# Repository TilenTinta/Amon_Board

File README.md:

# Amon Board — Flight Controller & Firmware

**Project Status:** In Progress

# Description:
Flight controller hardware and firmware used in the Amon Lander project. Two hardware lines are maintained:
- **Board v1 (ESP32 WROOM-32)** — never released (critical error).
- **Board v2 (STM32F405)** — the current, working design.
- **Board v3 (STM32H743VIT6)** — in development.
- **Board v4 (STM32xxx (Zephyr) + Raspberry Pi CM4)** — the next-gen design with a new MCU running Zephyr RTOS and a companion **Raspberry Pi Compute Module 4 (CM4)**.

> Part of the Amon Lander project:
>
> - **Amon Lander** — overall vehicle, frame, test/control SW, and data  
>   https://github.com/TilenTinta/Amon_Lander  
> - **Amon Link** — PC - drone communications (PCB + firmware)  
>   https://github.com/TilenTinta/Amon_Link  
> - **Amon Ground Control** — desktop GCS for telemetry & control  
>   https://github.com/TilenTinta/Amon_GroundControl_Software

---

## Table of Contents

- [Overview](#overview)
- [Hardware Versions](#hardware-versions)
  - [Board v2 — STM32F405](#board-v1--stm32f405)
  - [Board v3 — STM32H743](#board-v1--stm32h743)
  - [Board v4 — Zephyr + CM4](#board-v2--zephyr--cm4)
- [Version Matrix](#version-matrix)
- [Repository Structure](#repository-structure)
- [Getting Started](#getting-started)
  - [Build & Flash: Board v2 & v3](#build--flash-board-v1)
  - [Build & Flash: Board v4 (Zephyr)](#build--flash-board-v2-zephyr)
  - [First Boot: CM4 Companion](#first-boot-cm4-companion)
- [Calibration & Testing](#calibration--testing)
- [Roadmap](#roadmap)
- [Status & Disclaimer](#status--disclaimer)
- [License](#license)
- [Acknowledgments](#acknowledgments)

---

## Overview

This board is a custom flight controller for **Amon Lander**. The **v2** generation uses an **STM32F405RGT6 (LQFP-64)** and a hand-written firmware stack (drivers from scratch, for learning and control). Because of the flight algorithm planned to be used in this project, the decision was made to modify the current **v2** PCB with a new MCU. This is the **STM32H743VIT6 (LQFP-100)** and to fix some issues and add features that were missing or incorrect in the previous version. A **v3** generation is being designed around a **Zephyr-supported MCU** for real-time control, that will be paired with a **Raspberry Pi CM4** for high-level tasks (GCS link, logging, navigation stack, future CV/ML, etc.) in **v4**.

Everything was built from the ground up — **electronics, firmware, and software**. Most tools used are **free** and widely available to makers. Expect a learning-first approach over simplicity: some solutions could be easier, but the point is to **learn and explore**.

---

## Hardware Versions

### Board v1 — ESP32 WROOM-32

**Highlights**

- **MCU:** ESP32 WROOM-32 module
- **Power & Protection**
  - Dual vertical **XT60** inputs (PCB PWR and EDF voltage)
  - **Reverse-polarity diode**
  - Max input tested: **12 V**
  - Two **LDO regulators**: 3.3V (MCU/sensors) & 5V/5A (servos)
- **Sensors**
  - **MPU6050** (IMU)
  - **BME280** (temp/pressure/humidity)
  - TOF connector for **VL53L1X**
- **Navigation & Comms**
  - **GPS** connector (GY-NEO6MV2)
  - **single NRF24L01+ PA/LNA** (RX–TX) module
  - **ESP32 WiFi** can be used for communication
- **I/O**
  - **PWM:** 4× servos + 1× EDF
  - Expansion: **SPI** & **I²C** headers
  - **USB** with surge protection (over CH340C)
  - **4-pin JTAG** header
  - **RGB status LED**
  - **Buzzer**
- **Storage:** **microSD** slot
- **PCB:** 4-layer

**Firmware (v1)**
- **Status:** Never really worked (ESP32 was eliminated from the project)

### Board v2 — STM32F405

**Highlights**

- **MCU:** STM32F405RGT6 (LQFP-64) - Cortex M4, 168MHz, 196kB RAM, 1MB Flash
- **Power & Protection**
  - Dual vertical **XT60** inputs (PCB PWR and EDF voltage)
  - **Reverse-polarity diode**
  - Max input tested: **12 V**
  - Two **buck regulators**: 3.3 V (MCU/sensors) & 5 V (servos), ~5 A each
- **Switching/Startup:** Power-on by battery insertion or external switch on a terminal
- **Grounding:** Grounded mounting holes
- **Sensors**
  - **MPU6050** (IMU)
  - **BME280** (temp/pressure/humidity)
  - **HMC5883L** (compass) *added later
  - TOF connector for **VL53L1X**
- **Navigation & Comms**
  - **GPS** connector (GY-NEO6MV2; also reused for calibration)
  - **2× NRF24L01+ PA/LNA** (RX–TX)
- **I/O**
  - **PWM:** 4× servos + 1× EDF (configurable)
  - Expansion: **SPI** & **I²C** headers
  - **USB OTG** with surge protection
  - **10-pin JTAG** header
  - **RGB status LED**
- **Storage:** External flash (telemetry) + **microSD** slot
- **PCB:** 4-layer, working but slated for a future revision/refresh

**Firmware (v2)**

- **Approach:** Minimal dependencies; **drivers from scratch** (for learning)  
- **Status:** Runs and evolves; some drivers may still have rough edges  
- **Focus:** Bring-up, sensor fusion, basic control loops, telemetry logging and transmition...

> 

### Board v3 — STM32H743

**Highlights**

- **MCU:** STM32H743VIT66 (LQFP-100) - Cortex M7, 480MHz, 1MB RAM, 2MB Flash
- **Power & Protection**
  - Dual horizontal **XT60** inputs (PCB PWR and EDF voltage)
  - **Reverse-polarity diode**
  - Max input tested: **12 V**
  - Three **buck regulators**: 3.3 V (MCU/sensors) & 5 V (ESC and placeholder) & 7.2 V (servos), ~5 A each + more stable voltage
- **Switching/Startup:** Power-on sequence 3.3V -> 5V -> 7.2V (monitoring of regulators output voltages and enable/disable function)
- **Grounding:** Grounded mounting holes
- **Sensors**
  - **MPU6050** (IMU)
  - **BME280** (temp/pressure/humidity)
  - **HMC5883L** (compass)
  - Connector for TOF - **VL53L1X**
  - Connector for optical flow - **PMW3901**
- **Navigation & Comms**
  - Connector for GPS module -**GY-NEO6MV2**
  - **2× NRF24L01+ PA/LNA** (RX–TX) now on PCB - eliminated use of modules
  - **USB** over serial chip (CH340G) - eliminated use of USB OTG
- **I/O**
  - **PWM:** 4× servos + 1× EDF
  - Expansion: **SPI** & **I²C** headers
  - **10-pin JTAG** header (Olimex HAB-VCR-010-LF)
  - **RGB status LED**
  - **Single RED status LED**
  - Three connector low **LED modules** and additional AUX connector for future use
- **Storage:** External flash (telemetry) + **microSD** slot
- **PCB:** 4-layer

**Firmware (v3)**

- **Base:** Firmware is fully based on **Firmware v2**
- **Approach:** Minimal dependencies; **drivers from scratch** (for learning)  
- **Status:** Runs and evolves; some drivers may still have rough edges  
- **Focus:** sensor fusion, advance control algorithms, telemetry logging and transmition...

> 

---

### Board v4 — Zephyr + CM4

**Architecture (planned / in development)**

- **Real-time MCU (Zephyr)**  
  - New MCU (TBD; Zephyr-supported) handles **Real-time**:
    - Sensor acquisition & fusion
    - Control loops (attitude/rate, TVC/actuators, EDF control)
    - Safety interlocks & failsafes
    - Deterministic logging (to QSPI flash / SD)
  - **Zephyr RTOS** app with:
    - Devicetree-based pin/peripheral config
    - Workqueues/threads for IMU, baro, magnetometer, TOF, PWM
    - Shell/CLI over UART/USB for diagnostics
    - Config storage (NVS) and firmware update hooks

- **Companion Computer — Raspberry Pi CM4**  
  - Runs services for:
    - Ground link, mission control, high-rate logging
    - Navigation stack expansion (mapping, state estimation helpers)
    - Future CV/ML applications (optional)
  - **Link to MCU:** UART (primary) + SPI/CAN (optional)  
  - **Services:** Telemetry bridge (to Amon Link), data recorder, configuration UI server
  - **OS:** Raspberry Pi OS Lite (or other lightweight Linux)

**Electrical**
- Robust power tree with multiple separated rails for servos/EDF vs logic
- MCU - CM4 isolation where needed (level shifting/ESD)
- On-board mass storage for logs (eMMC on CM4 + SD/QSPI on MCU)
- External debug: SWD/JTAG for MCU; USB-C or Ethernet for CM4

**Firmware (v4)**

- **Zephyr** application (modules: sensors, control, comms, storage)
- **IPC format:** CBOR/Protobuf frame over UART (CRC-guarded)
- **Bootloaders & Updates:** MCU bootloader (serial/DFU), CM4 apt-based or containerized deployment
- **Testing:** HIL hooks; replay logs for control tuning

---

## Version Matrix

## Version Matrix

| Capability                  | Board v1 — ESP32 | Board v2 — STM32F405 | Board v3 — STM32H743 | Board v4 — Zephyr + CM4 |
|----------------------------|------------------|----------------------|----------------------|--------------------------|
| MCU                         | ESP32 WROOM-32   | STM32F405RGT6        | STM32H743VIT6        | **TBD (Zephyr-supported)** |
| RTOS                        | None             | None (bare-metal)    | None (bare-metal)    | **Zephyr RTOS**          |
| Companion Computer          | —                | —                    | —                    | **Raspberry Pi CM4**     |
| Sensors                     | MPU6050, BME280, VL53L1X | MPU6050, BME280, HMC5883L, VL53L1X | MPU6050, BME280, HMC5883L, VL53L1X | Same class; final selection TBD |
| Radio                       | 1× NRF24L01+ PA/LNA | 2× NRF24L01+ PA/LNA | 2× NRF24L01+ PA/LNA | TBD (NRF / other via MCU or CM4) |
| Navigation                  | GPS (GY-NEO6MV2) | GPS (GY-NEO6MV2)     | GPS (GY-NEO6MV2)     | GPS via MCU or CM4 module |
| Storage                     | microSD          | Flash + microSD      | Flash + microSD      | CM4 eMMC + MCU flash/SD  |
| USB                         | USB (CH340C)     | USB OTG              | USB OTG + CH340G     | USB (MCU + CM4)          |
| Programming / Debug         | 4-pin JTAG       | 10-pin JTAG          | 10-pin JTAG          | SWD/JTAG (MCU) + SSH/USB/Ethernet (CM4) |
| PWM Outputs                 | 4× servos + 1× EDF | 4× servos + 1× EDF | 4× servos + 1× EDF | Same (handled by MCU)    |
| Expansion                   | SPI, I²C         | SPI, I²C             | SPI, I²C             | SPI, I²C, UART, CAN (planned) |
| Power                       | XT60, LDO (3.3V + 5V/5A) | XT60, buck (3.3V + 5V/5A + 7.2V) | XT60, improved buck (3.3V + 5V/5A) | Segregated rails, higher headroom (TBD) |
| PCB                         | 4-layer          | 4-layer              | 4-layer              | TBD                      |
| Firmware Status             | Not working    | Working, evolving | In development | In development        |
| Firmware Approach           | —                | Bare-metal, custom drivers | Based on v2, improved | Zephyr modules + Linux services |
| Firmware Updates            | USB              | JTAG/SWD/DFU         | JTAG/SWD/DFU         | MCU bootloader + CM4 (apt/container) |

---

## Getting Started

### Build & Flash: Board v1

1. **Clone**
   ```bash
   git clone https://github.com/<your-org-or-user>/Amon_Board.git
   cd Amon_Board/firmware/Amon_board_firmware-MCU
   ```
2. **Toolchain**
   - Install `arm-none-eabi-gcc` and your preferred STM32 flashing tool.
3. **Configure - can be automatic**
   - Target: **STM32F405RG**; enable FPU; set clock tree; verify linker script.
4. **Build**
   ```bash
   make
   ```
   or use your IDE’s Build action.
5. **Flash**
   - Via **JTAG/SWD** (10-pin header) using your probe (ST-Link, J-Link, etc.).
6. **Verify**
   - Rails at 5 V/3.3 V, sensor presence on I²C/SPI, status RGB LED patterns.

---

### Build & Flash: Board v2 (Zephyr)
Instructions bellow are only "place holder". Detailed instructions will be provided once the development will be started. For flashing and debugging will be used Segger Ozone software.

1. **Prerequisites**
   - Install **Zephyr SDK**, Python, CMake, Ninja.
   - Install **west**: `pip install west`
2. **Get Sources**
   ```bash
   cd Amon_Board/firmware/v2-zephyr
   west init -l .
   west update
   ```
3. **Board Definition**
   - Use the custom board under `boards/amon_v2/` (edit SoC, pins, clocks, and flash layout as needed).
4. **Build**
   ```bash
   west build -b amon_v2 app
   ```
5. **Flash**
   ```bash
   west flash
   ```
6. **Console**
   ```bash
   west espressif monitor   # or 'west zephyr monitor' / minicom, depending on target
   ```
   *(Choose the appropriate monitor command for your MCU/OS.)*

---

### First Boot: CM4 Companion

1. **Flash OS**
   - Install **Raspberry Pi OS Lite** to CM4’s eMMC or carrier-board storage.
2. **Enable Interfaces**
   - `sudo raspi-config` → enable UART, I2C, SPI as needed.
3. **Install Services**
   ```bash
   sudo apt update
   sudo apt install python3-pip git
   git clone https://github.com/<your-org-or-user>/amon-cm4-services.git
   cd amon-cm4-services && ./install.sh
   ```
   - Starts a telemetry bridge (serial↔TCP/gRPC), data logger, and config UI.
4. **Connect to MCU**
   - Wire UART (and optionally SPI/CAN) between CM4 and MCU.
   - Confirm link with a ping/handshake command.
5. **Network Access**
   - SSH into CM4; forward telemetry to **Amon Ground Control** over Wi-Fi/Ethernet.

---

## Calibration & Testing

- **GPS/Calibration Port:** The v2 GPS connector doubles as a calibration interface during bring-up. PCB v3 do this over USB.  
- **Telemetry:** Log to external flash/microSD (v2 & v3) or CM4 eMMC + MCU storage (v4).  
- **LED Status:** On-board RGB LED signals power, init, errors, and link status.  
- **HIL/Replay (v2):** Reproduce flights by streaming recorded sensor frames back into the MCU (for controller tuning).

---

## Roadmap

- **v1**
   - Failed design
- **v2**
  - Incremental driver fixes and documentation cleanup
  - Manufacturing files refresh (Gerbers/BOM/PNP)
- **v3**
   - Modified v2 design with new MCU, connectors, sensors
   - Modified v2 firmware for new MCU (much higher clock: 168 MHz -> 480MHz)
   - Development of flight algorithm and controller + first flights 
- **v4**
  - Finalize MCU choice and Zephyr board port
  - Define IPC schema (CBOR/Proto) & reliability (CRC/seq/ACK)
  - CM4 services (logger, bridge, config UI)
  - Development of new flight algorithm and controllers + flights 

---

## Status & Disclaimer

- **Works, but in progress:** v2 firmware runs; development is active and some drivers may still have rough edges.  
- **New hardware incoming:** v2/v3/v4 will introduce a Zephyr-based MCU and CM4 companion; designs are evolving.

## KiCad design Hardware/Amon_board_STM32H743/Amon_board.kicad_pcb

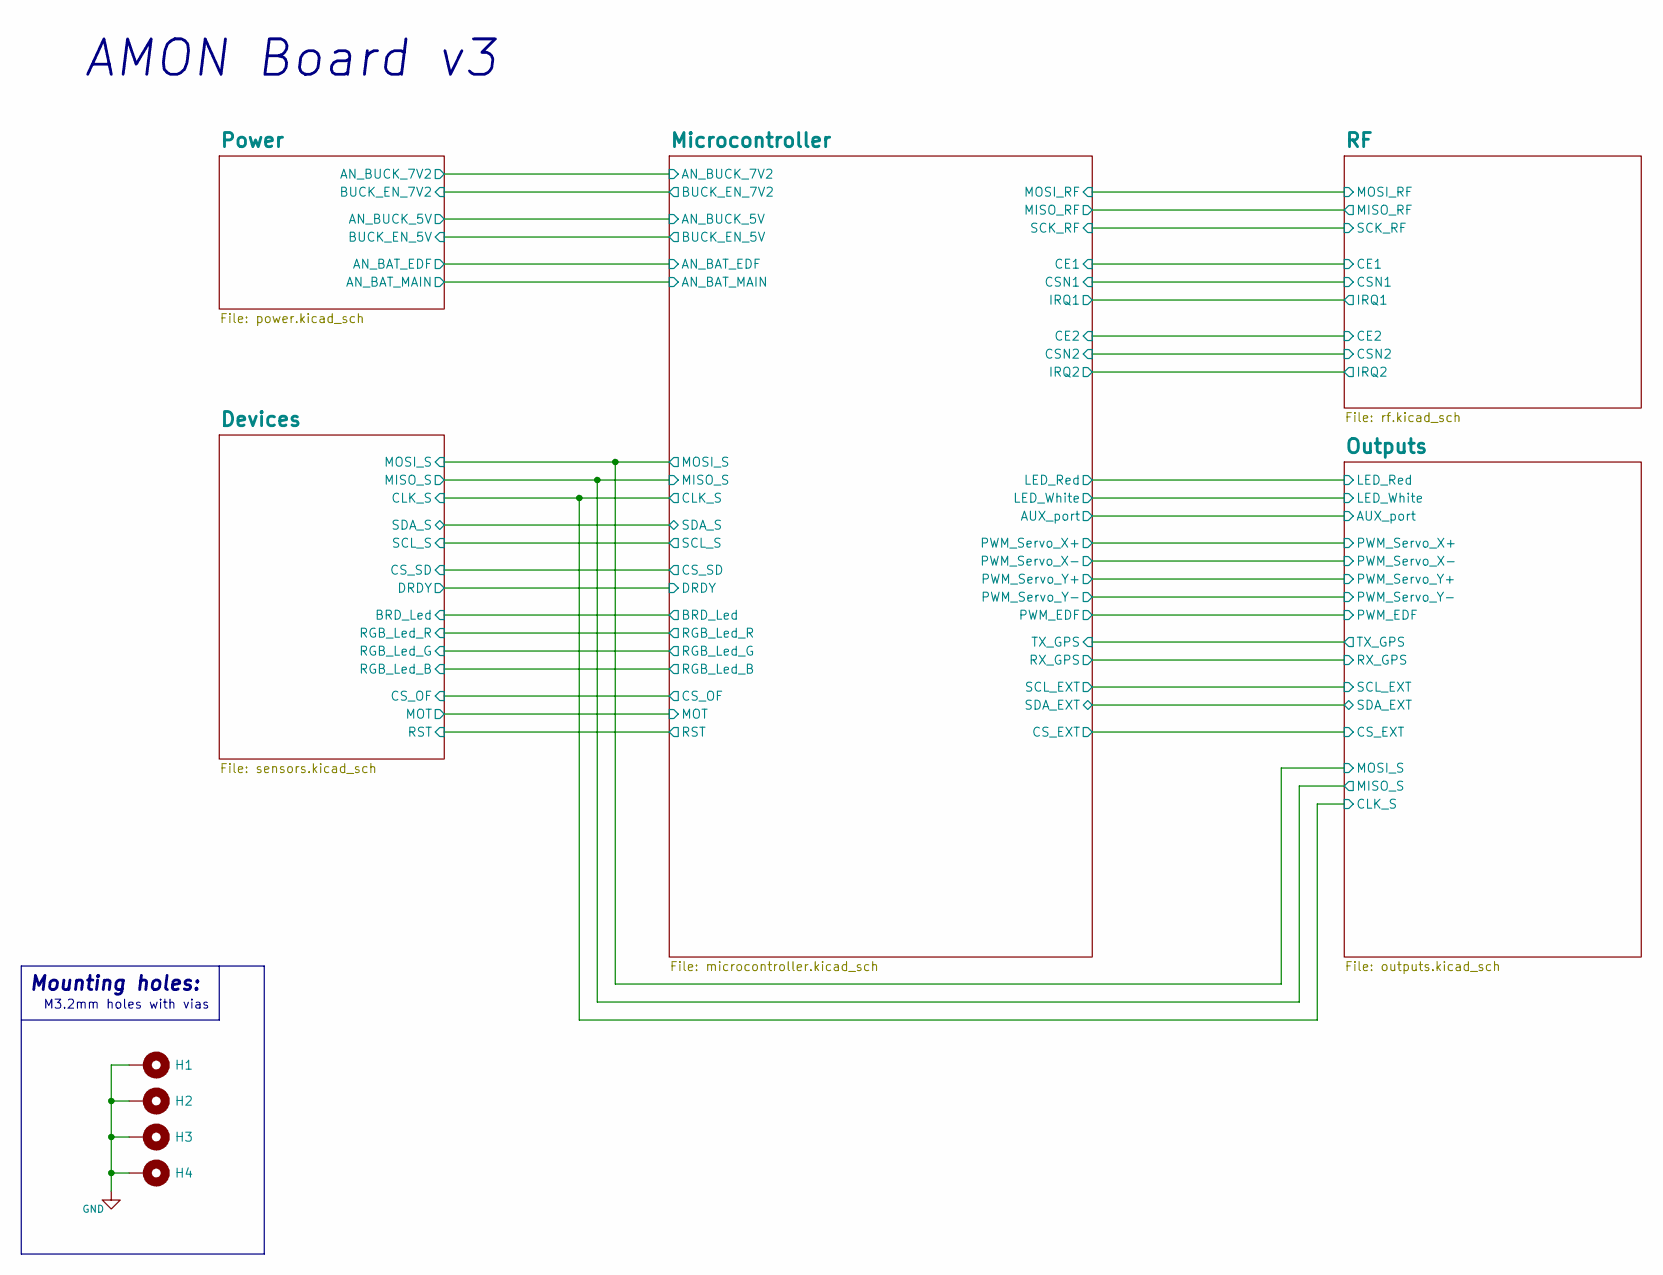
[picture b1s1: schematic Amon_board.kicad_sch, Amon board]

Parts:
H1, H2, H3, H4: MountingHole_Pad; MountingHole_3.2mm_M3_Pad_Via

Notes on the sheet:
M3.2mm holes with vias
Mounting holes:
AMON Board v3

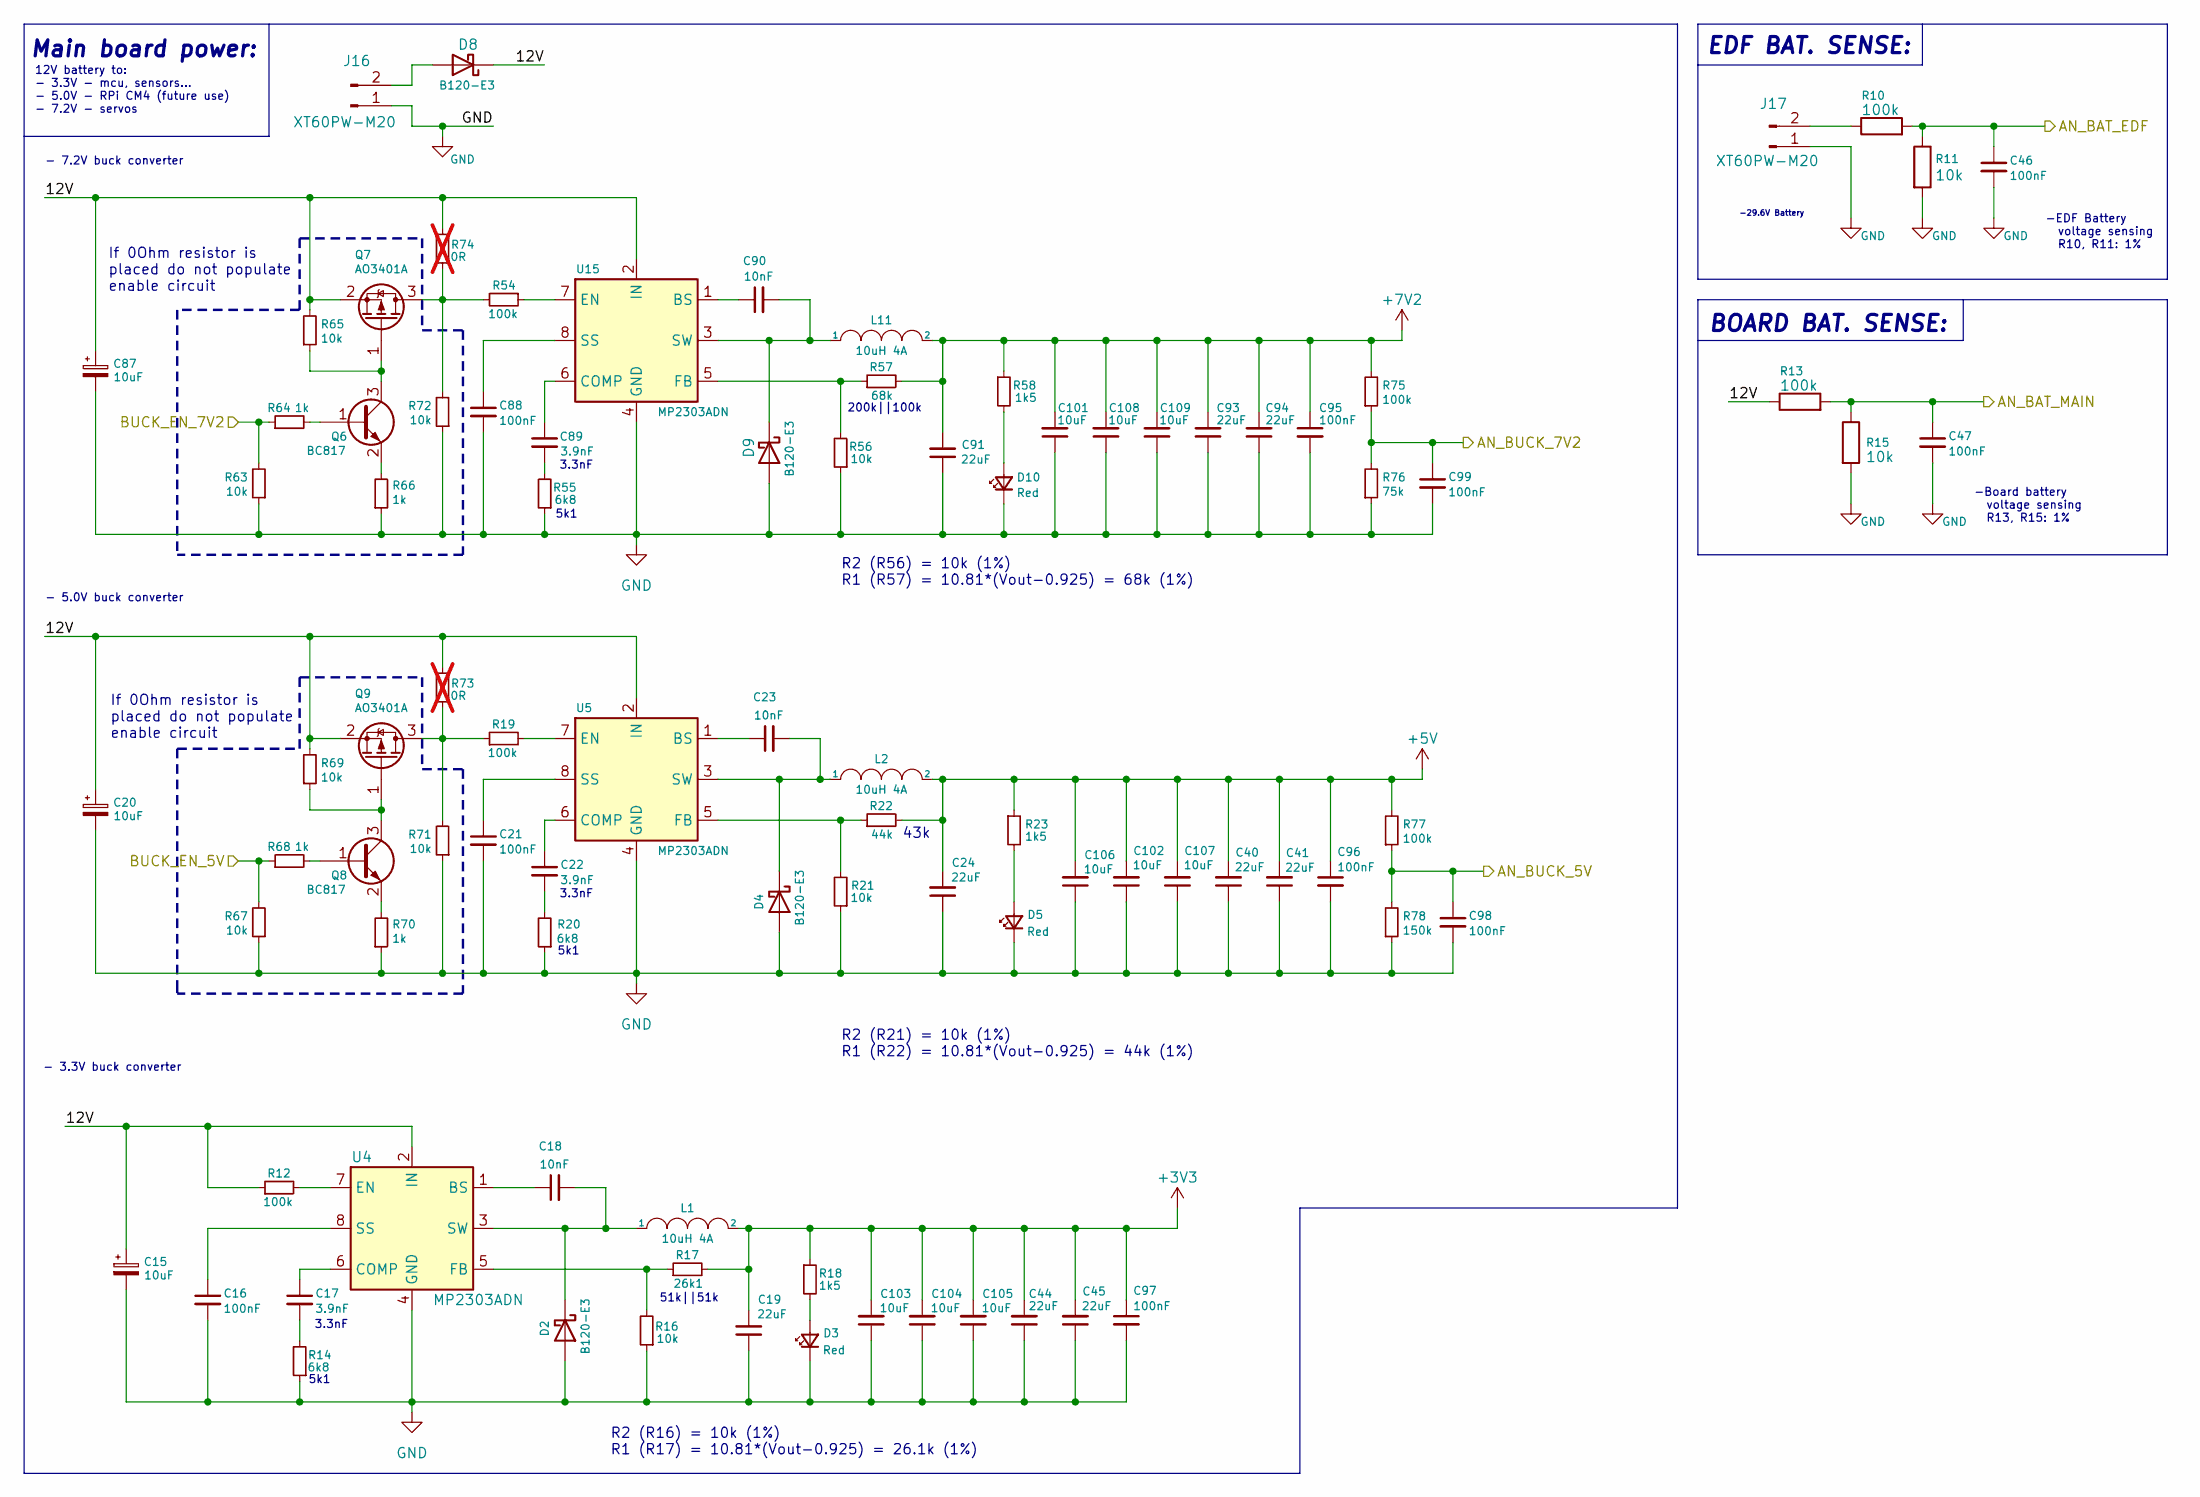
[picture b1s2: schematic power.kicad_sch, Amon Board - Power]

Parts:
C15, C20, C87: 10uF; CP_EIA-3216-10_Kemet-I
C16, C21, C46, C47, C88, C95, C96, C97, C98, C99: 100nF; C_0603_1608Metric
C17, C22, C89: 3.9nF; C_0603_1608Metric
C18, C23, C90: 10nF; C_0603_1608Metric
C19, C24, C40, C41, C44, C45, C91, C93, C94: 22uF; C_1206_3216Metric
C101, C102, C103, C104, C105, C106, C107, C108, C109: 10uF; C_1206_3216Metric
D2, D4, D8, D9: B120-E3; D_SMA
D3, D5, D10: Red; LED_0603_1608Metric
J16, J17: XT60PW-M20; AMASS_XT60PW-M_1x02_P7.20mm_Horizontal
L1, L2, L11: 10uH 4A; L_APV_APH0630
Q6, Q8: BC817; SOT-23
Q7, Q9: AO3401A; SOT-23
R10, R13: 100k; R_1206_3216Metric
R11, R15: 10k; R_1206_3216Metric
R12, R19, R54, R75, R77: 100k; R_0603_1608Metric
R14, R20, R55: 6k8; R_0603_1608Metric
R16, R21, R56, R63, R65, R67, R69, R71, R72: 10k; R_0603_1608Metric
R17: 26k1; R_0603_1608Metric
R18, R23, R58: 1k5; R_0603_1608Metric
R22: 44k; R_0603_1608Metric
R57: 68k; R_0603_1608Metric
R64, R66, R68, R70: 1k; R_0603_1608Metric
R73, R74: 0R; R_0603_1608Metric; not fitted
R76: 75k; R_0603_1608Metric
R78: 150k; R_0603_1608Metric
U4, U5, U15: MP2303ADN; SOIC-8-1EP_3.9x4.9mm_P1.27mm_EP2.62x3.51mm

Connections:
+5V: C24.2, C40.2, C41.2, C96.1, C102.2, C106.2, C107.2, L2.2, R22.2, R23.1, R77.2; also elsewhere on the board
+7V2: C91.2, C93.2, C94.2, C95.1, C101.2, C108.2, C109.2, L11.2, R57.2, R58.1, R75.2; also elsewhere on the board
/Microcontroller/AN_BAT_EDF: C46.1, R10.2, R11.1; also elsewhere on the board
/Microcontroller/AN_BAT_MAIN: C47.1, R13.2, R15.1; also elsewhere on the board
/Microcontroller/AN_BUCK_5V: C98.1, R77.1, R78.2; also elsewhere on the board
/Microcontroller/AN_BUCK_7V2: C99.1, R75.1, R76.2; also elsewhere on the board
/Microcontroller/BUCK_EN_5V: R67.2, R68.1; also elsewhere on the board
/Microcontroller/BUCK_EN_7V2: R63.2, R64.1; also elsewhere on the board
/Power/12V: C15.1, C20.1, C87.1, D8.1 (K), Q7.2 (S), Q9.2 (S), R12.1, R13.1, R65.2, R69.2, R73.2, R74.2, U4.2 (IN), U5.2 (IN), U15.2 (IN)
unnamed: C17.2, R14.2
unnamed: C22.2, R20.2
unnamed: C89.2, R55.2
unnamed: C18.2, D2.1 (K), L1.1, U4.3 (SW)
unnamed: D3.2 (A), R18.2
unnamed: C23.2, D4.1 (K), L2.1, U5.3 (SW)
unnamed: D5.2 (A), R23.2
unnamed: D8.2 (A), J16.2
unnamed: C90.2, D9.1 (K), L11.1, U15.3 (SW)
unnamed: D10.2 (A), R58.2
unnamed: J17.2, R10.1
unnamed: Q6.1 (B), R64.2
unnamed: Q6.3 (C), Q7.1 (G), R65.1
unnamed: Q6.2 (E), R66.2
unnamed: Q7.3 (D), R54.2, R72.2, R74.1
unnamed: Q8.1 (B), R68.2
unnamed: Q8.3 (C), Q9.1 (G), R69.1
unnamed: Q8.2 (E), R70.2
unnamed: Q9.3 (D), R19.1, R71.2, R73.1
unnamed: C18.1, U4.1 (BS)
unnamed: C17.1, U4.6 (COMP)
unnamed: R12.2, U4.7 (EN)
unnamed: R16.2, R17.1, U4.5 (FB)
unnamed: C16.1, U4.8 (SS)
unnamed: C23.1, U5.1 (BS)
unnamed: C22.1, U5.6 (COMP)
unnamed: R19.2, U5.7 (EN)
unnamed: R21.2, R22.1, U5.5 (FB)
unnamed: C21.1, U5.8 (SS)
unnamed: C90.1, U15.1 (BS)
unnamed: C89.1, U15.6 (COMP)
unnamed: R54.1, U15.7 (EN)
unnamed: R56.2, R57.1, U15.5 (FB)
unnamed: C88.1, U15.8 (SS)

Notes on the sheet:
-Board battery voltage sensing R13, R15: 1%
51k||51k
200k||100k
- 7.2V buck converter
R2 (R56) = 10k (1%) R1 (R57) = 10.81*(Vout-0.925) = 68k (1%)
- 5.0V buck converter
BOARD BAT. SENSE:
5k1
-29.6V Battery
-EDF Battery voltage sensing R10, R11: 1%
If 0Ohm resistor is placed do not populate enable circuit
12V battery to: - 3.3V - mcu, sensors... - 5.0V - RPi CM4 (future use) - 7.2V - servos
- 3.3V buck converter
3.3nF
EDF BAT. SENSE:
R2 (R21) = 10k (1%) R1 (R22) = 10.81*(Vout-0.925) = 44k (1%)
43k
Main board power:
R2 (R16) = 10k (1%) R1 (R17) = 10.81*(Vout-0.925) = 26.1k (1%)

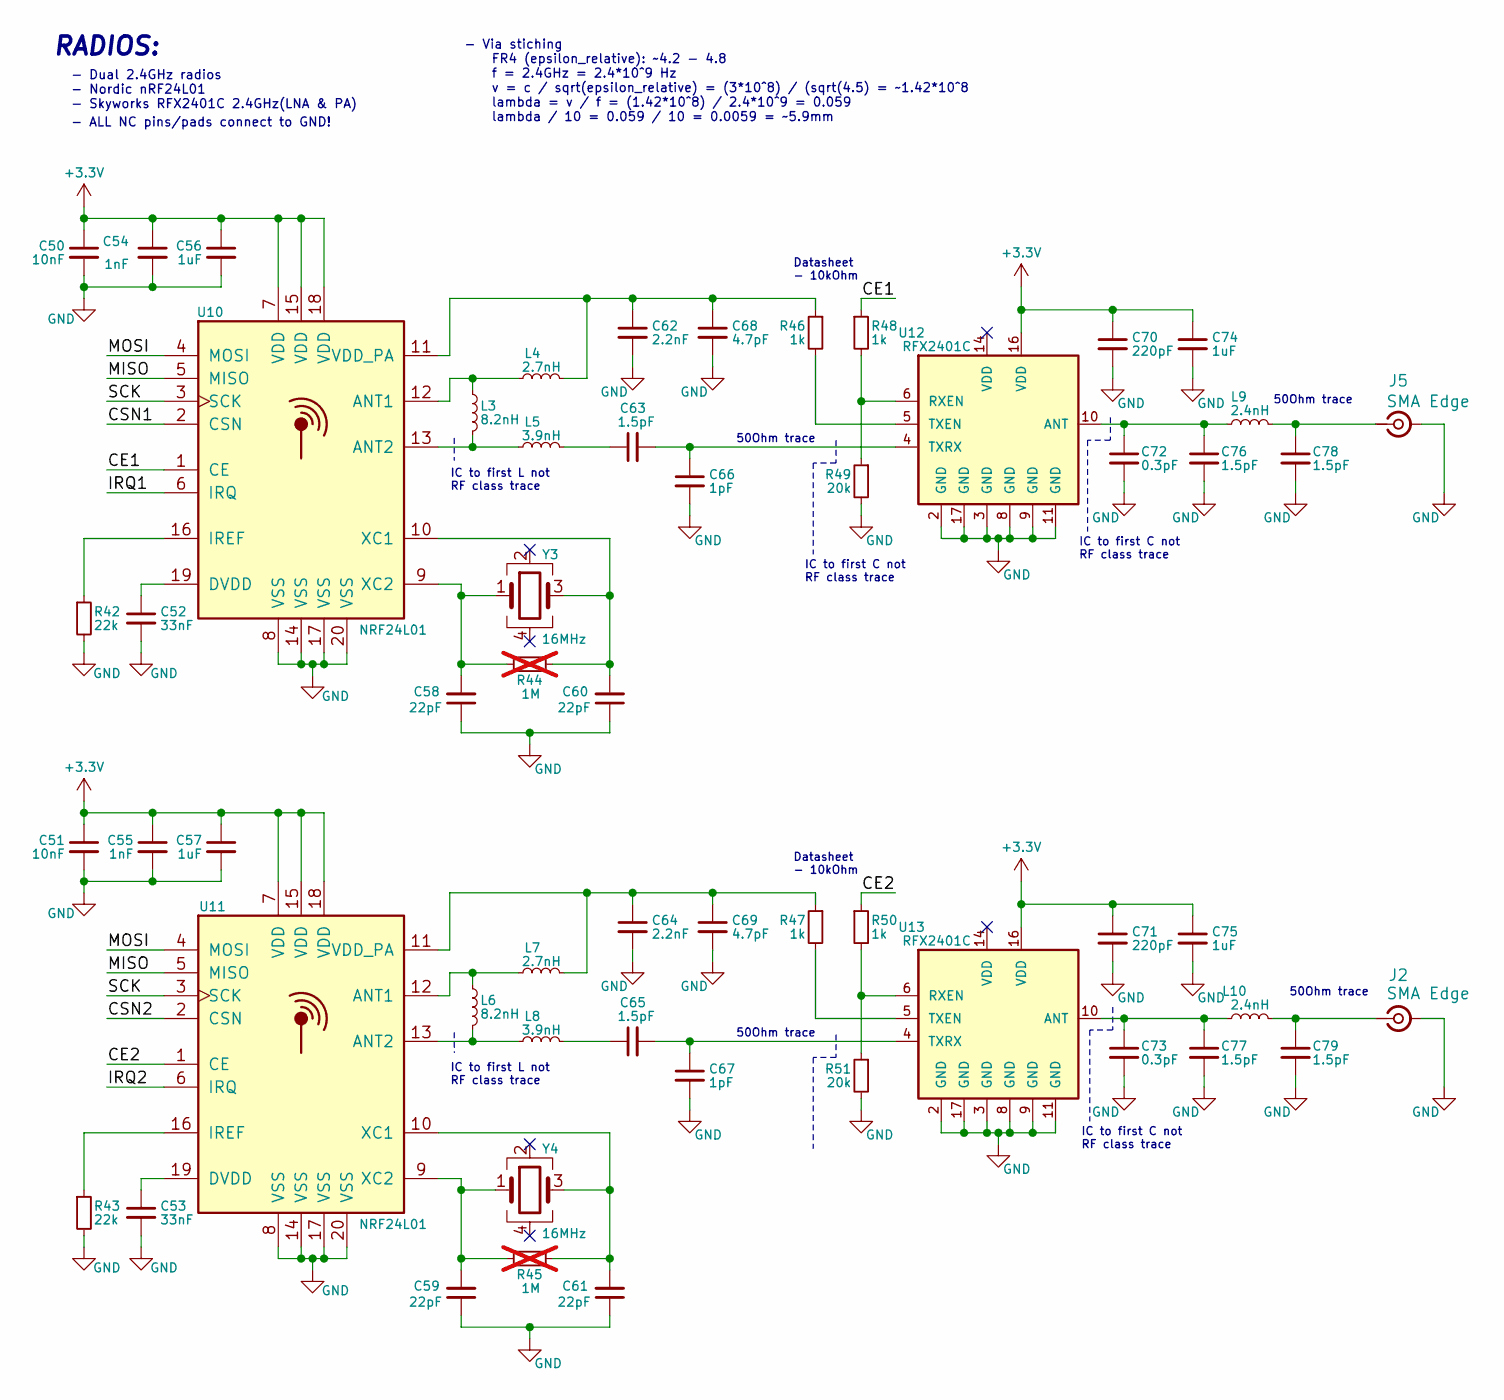
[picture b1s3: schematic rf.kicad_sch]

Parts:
C50, C51: 10nF; C_0402_1005Metric
C52, C53: 33nF; C_0402_1005Metric
C54, C55: 1nF; C_0402_1005Metric
C56, C57, C74, C75: 1uF; C_0402_1005Metric
C58, C59, C60, C61: 22pF; C_0402_1005Metric
C62, C64: 2.2nF; C_0402_1005Metric
C63, C65, C76, C77, C78, C79: 1.5pF; C_0402_1005Metric
C66, C67: 1pF; C_0402_1005Metric
C68, C69: 4.7pF; C_0402_1005Metric
C70, C71: 220pF; C_0402_1005Metric
C72, C73: 0.3pF; C_0402_1005Metric
J2, J5: SMA Edge; SMA_Samtec_SMA-J-P-X-ST-EM1_EdgeMount
L3, L6: 8.2nH; L_0402_1005Metric
L4, L7: 2.7nH; L_0402_1005Metric
L5, L8: 3.9nH; L_0402_1005Metric
L9, L10: 2.4nH; L_0402_1005Metric
R42, R43: 22k; R_0402_1005Metric
R44, R45: 1M; R_0402_1005Metric; not fitted
R46, R47, R48, R50: 1k; R_0402_1005Metric
R49, R51: 20k; R_0402_1005Metric
U10, U11: NRF24L01; QFN-20-1EP_4x4mm_P0.5mm_EP2.5x2.5mm
U12, U13: RFX2401C; QFN50P300X300X60-17N
Y3, Y4: 16MHz; Crystal_SMD_3225-4Pin_3.2x2.5mm

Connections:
/Microcontroller/CSN1: U10.2 (CSN); also elsewhere on the board
/Microcontroller/CSN2: U11.2 (CSN); also elsewhere on the board
/Microcontroller/IRQ1: U10.6 (IRQ); also elsewhere on the board
/Microcontroller/IRQ2: U11.6 (IRQ); also elsewhere on the board
/Microcontroller/MISO_RF: U10.5 (MISO), U11.5 (MISO); also elsewhere on the board
/Microcontroller/MOSI_RF: U10.4 (MOSI), U11.4 (MOSI); also elsewhere on the board
/Microcontroller/SCK_RF: U10.3 (SCK), U11.3 (SCK); also elsewhere on the board
/RF/CE1: R48.1, U10.1 (CE); also elsewhere on the board
/RF/CE2: R50.1, U11.1 (CE); also elsewhere on the board
unnamed: C63.1, L5.2
unnamed: C65.1, L8.2
unnamed: L3.1, L4.1, U10.12 (ANT1)
unnamed: L3.2, L5.1, U10.13 (ANT2)
unnamed: C52.1, U10.19 (DVDD)
unnamed: R42.1, U10.16 (IREF)
unnamed: C62.1, C68.1, L4.2, R46.1, U10.11 (VDD_PA)
unnamed: C60.2, R44.2, U10.10 (XC1), Y3.3
unnamed: C58.2, R44.1, U10.9 (XC2), Y3.1
unnamed: L6.1, L7.1, U11.12 (ANT1)
unnamed: L6.2, L8.1, U11.13 (ANT2)
unnamed: C53.1, U11.19 (DVDD)
unnamed: R43.1, U11.16 (IREF)
unnamed: C64.1, C69.1, L7.2, R47.1, U11.11 (VDD_PA)
unnamed: C61.2, R45.2, U11.10 (XC1), Y4.3
unnamed: C59.2, R45.1, U11.9 (XC2), Y4.1
unnamed: C72.1, C76.1, L9.1, U12.10 (ANT)
unnamed: R48.2, R49.1, U12.6 (RXEN)
unnamed: R46.2, U12.5 (TXEN)
unnamed: C63.2, C66.1, U12.4 (TXRX)
unnamed: C73.1, C77.1, L10.1, U13.10 (ANT)
unnamed: R50.2, R51.1, U13.6 (RXEN)
unnamed: R47.2, U13.5 (TXEN)
unnamed: C65.2, C67.1, U13.4 (TXRX)

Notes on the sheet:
50Ohm trace
- ALL NC pins/pads connect to GND!
IC to first C not RF class trace
- Dual 2.4GHz radios - Nordic nRF24L01 - Skyworks RFX2401C 2.4GHz(LNA & PA)
Datasheet - 10kOhm
- Via stiching FR4 (epsilon_relative): ~4.2 - 4.8 f = 2.4GHz = 2.4*10^9 Hz v = c / sqrt(epsilon_relative) = (3*10^8) / (sqrt(4.5) = ~1.42*10^8 lambda = v / f = (1.42*10^8) / 2.4*10^9 = 0.059 lambda / 10 = 0.059 / 10 = 0.0059 = ~5.9mm
RADIOS:
IC to first L not RF class trace

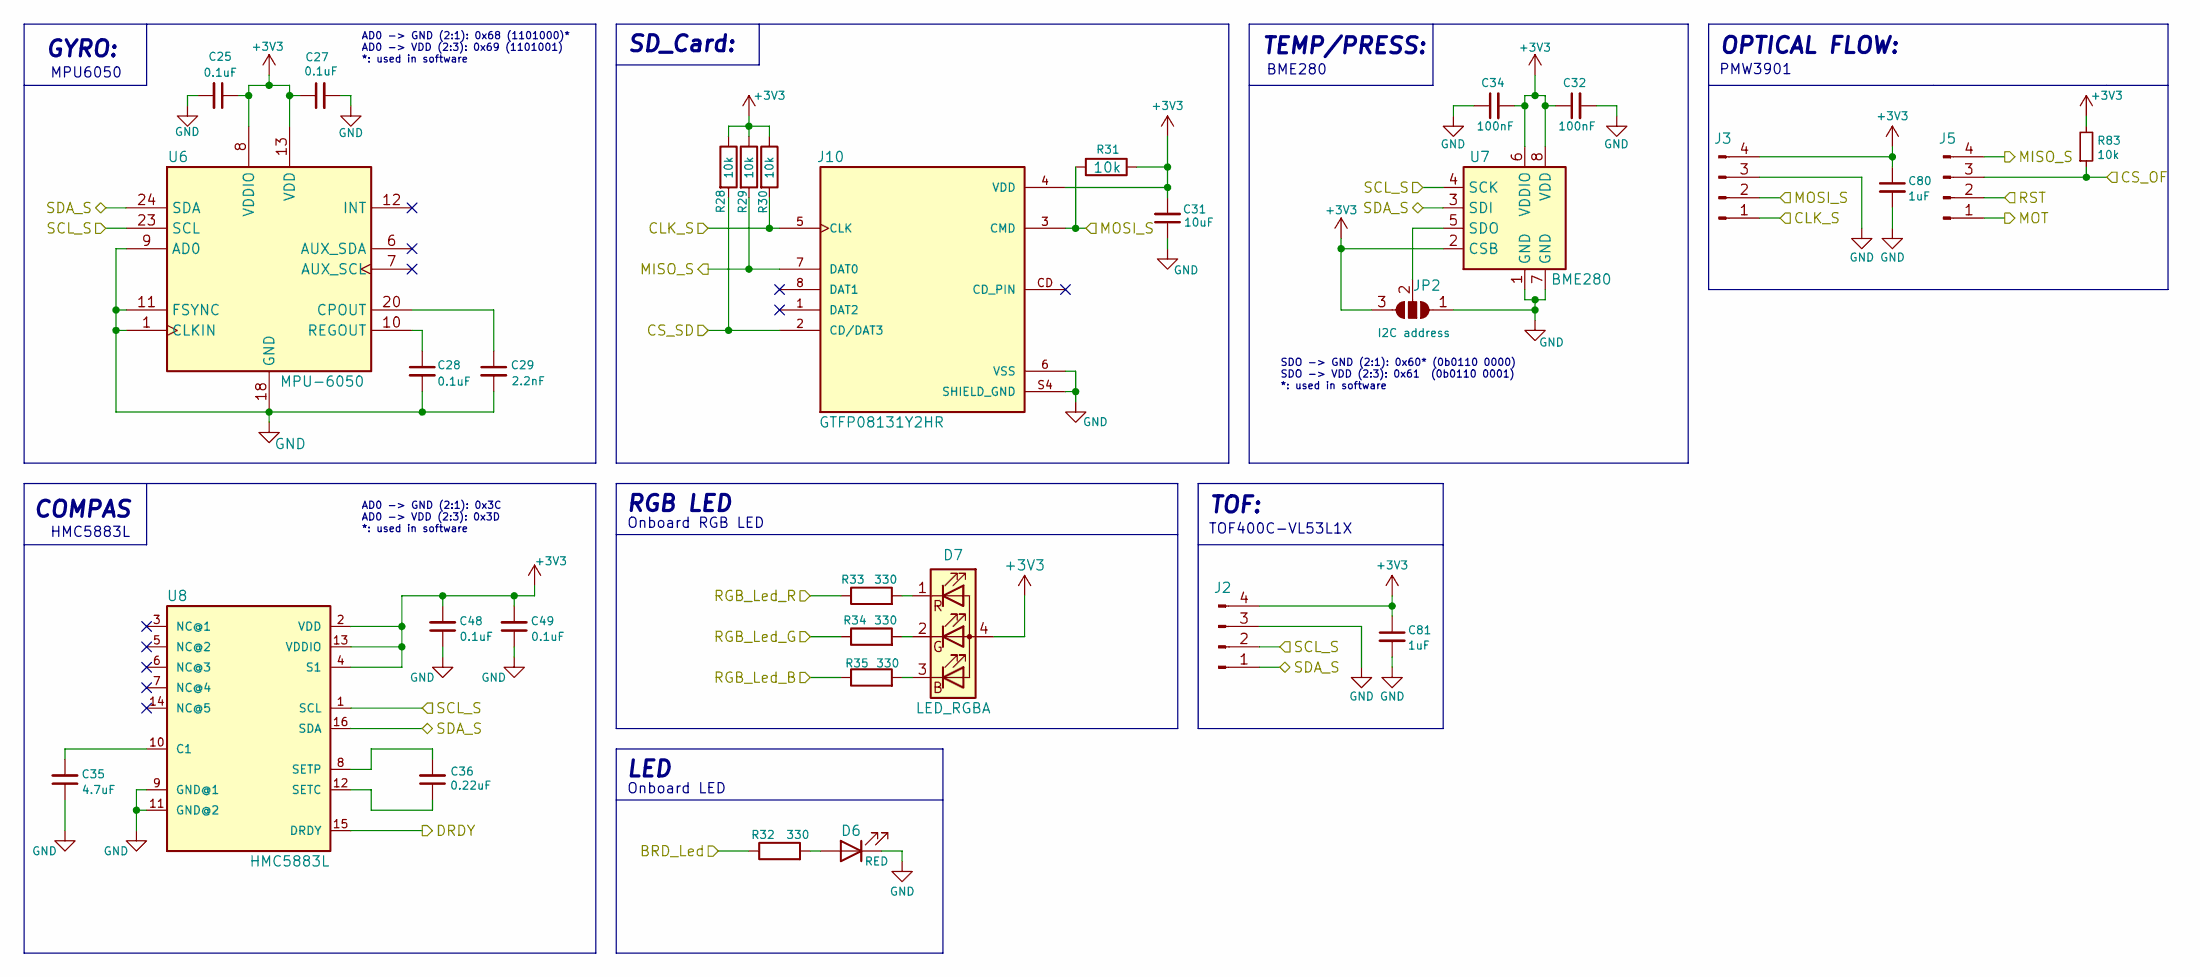
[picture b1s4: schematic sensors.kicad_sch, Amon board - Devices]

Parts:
C25, C27, C28, C48, C49: 0.1uF; C_0603_1608Metric
C29: 2.2nF; C_0603_1608Metric
C31: 10uF; C_0603_1608Metric
C32, C34: 100nF; C_0603_1608Metric
C35: 4.7uF; C_0603_1608Metric
C36: 0.22uF; C_0603_1608Metric
C80, C81: 1uF; C_0603_1608Metric
D6: RED; LED_0603_1608Metric
D7: LED_RGBA; LED_Cree-PLCC4_3.2x2.8mm_CCW
J2, J3, J5: Conn_01x04_Pin; JST_EH_S4B-EH_1x04_P2.50mm_Horizontal
J10: GTFP08131Y2HR; AMPHENOL_GTFP08131Y2HR; PARTREV A
JP2: I2C address; SolderJumper-3_P1.3mm_Open_RoundedPad1.0x1.5mm_NumberLabels
R28, R29, R30, R31, R83: 10k; R_0603_1608Metric
R32, R33, R34, R35: 330; R_0603_1608Metric
U6: MPU-6050; InvenSense_QFN-24_4x4mm_P0.5mm
U7: BME280; Bosch_LGA-8_2x2.5mm_P0.65mm_ClockwisePinNumbering
U8: HMC5883L; LPCC-16

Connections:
/Devices/BRD_Led: R32.1; also elsewhere on the board
/Devices/CLK_S: J3.1, J10.5 (CLK), R30.2; also elsewhere on the board
/Devices/CS_OF: J5.3, R83.1; also elsewhere on the board
/Devices/CS_SD: J10.2 (CD/DAT3), R28.2; also elsewhere on the board
/Devices/DRDY: U8.15 (DRDY); also elsewhere on the board
/Devices/MISO_S: J5.4, J10.7 (DAT0), R29.2; also elsewhere on the board
/Devices/MOSI_S: J3.2, J10.3 (CMD), R31.2; also elsewhere on the board
/Devices/RGB_Led_B: R35.1; also elsewhere on the board
/Devices/RGB_Led_G: R34.1; also elsewhere on the board
/Devices/RGB_Led_R: R33.1; also elsewhere on the board
unnamed: D6.2 (A), R32.2
unnamed: D7.3 (BK), R35.2
unnamed: D7.2 (GK), R34.2
unnamed: D7.1 (RK), R33.2
unnamed: JP2.2 (C), U7.5 (SDO)
unnamed: C29.1, U6.20 (CPOUT)
unnamed: C28.1, U6.10 (REGOUT)
unnamed: C35.2, U8.10 (C1)
unnamed: C36.1, U8.12 (SETC)
unnamed: C36.2, U8.8 (SETP)

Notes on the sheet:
COMPAS
GYRO:
TOF:
AD0 -> GND (2:1): 0x3C AD0 -> VDD (2:3): 0x3D *: used in software
Onboard RGB LED
TEMP/PRESS:
AD0 -> GND (2:1): 0x68 (1101000)* AD0 -> VDD (2:3): 0x69 (1101001) *: used in software
LED
OPTICAL FLOW:
Onboard LED
HMC5883L
RGB LED
SD_Card:
PMW3901
SDO -> GND (2:1): 0x60* (0b0110 0000) SDO -> VDD (2:3): 0x61 (0b0110 0001) *: used in software
MPU6050
BME280
TOF400C-VL53L1X
